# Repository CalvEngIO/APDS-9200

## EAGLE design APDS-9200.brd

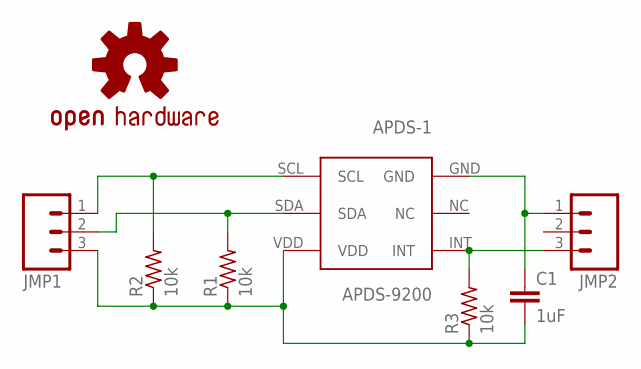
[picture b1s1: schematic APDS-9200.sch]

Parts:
APDS-1: APDS-9200
C1: 1uF; C0402
JMP1, JMP2: JMP-03; 1X03
LOGO1: OSHW-LOGOMINI; OSHW-LOGO-MINI
R1, R2, R3: 10k; R0402
U$1: CALVENGIO_HANDLEHANDLE.025; CALVENGIO_HANDLE.025

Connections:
unnamed: APDS-1.VDD, C1.2, JMP1.3 (4), R1.1, R2.1, R3.1
unnamed: APDS-1.GND, C1.1, JMP2.1 (2)
unnamed: APDS-1.INT, JMP2.3 (4), R3.2
unnamed: APDS-1.SDA, JMP1.2 (3), R1.2
unnamed: APDS-1.SCL, JMP1.1 (2), R2.2

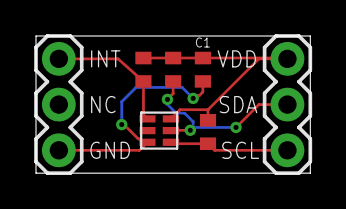
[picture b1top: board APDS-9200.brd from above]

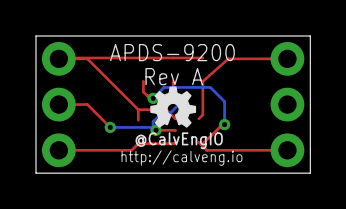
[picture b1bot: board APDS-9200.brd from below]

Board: 2 copper layers, 15.2 x 7.6 mm, 9 parts (2 on the bottom side), 5 nets.

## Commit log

2017-07-22 Added Silkscreen Items
2017-07-23 Fixed on board labels
2017-07-23 remove autosave files
2017-07-23 more updates
2017-08-06 more updates with reorganization and basic library read of light and uv values
2017-08-06 added Bill of Materials and datasheet
2017-08-18 changed drill size to 13mil to fit PCBWay guidelines
2017-09-02 Edited Interrupt Functionality
2017-09-04 Adjustments to interrupt functionality
